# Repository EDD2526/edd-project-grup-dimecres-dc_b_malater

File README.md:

View this project on [CADLAB.io](https://cadlab.io/project/30194). 

# Projecte Maleter 

>**Autors: Alba Martin i Mireia Campanera
<<<<<<< HEAD
>**Versió: 
=======
>**Versió: 1
>>>>>>> 689ee14ca79a34b128441d443d3a97a18ecf9688

----------

## Objectiu

>PCB per 
 - Obrir i tancar el maleter amb un motor
 - Detectar el peu sota el cotxe per obrir-lo
 - Activar el calefactor del vidre del maleter
 - Detectar objectes per evitar atrapaments

## Diagrama de blocs
<<<<<<< HEAD

=======

>>>>>>> 689ee14ca79a34b128441d443d3a97a18ecf9688
### Descripció/funcionalitat de cada bloc

  * El motor pot funcionar amb 12V de la bateria, però el microcontrolador en necessita 3.3V, per tant hem de posar reguladors de tensió que la redueixin.[Baixem de 12 a 5V (LM2596)] [Baixem de 5 a 3.3V (LM1117)]
  * Motor DC: un motor DC té dos cables, quan connectem una bateria, connectem un a 12V i l’altre a GND, i el motor comença a girar en un sentit. Què passa si canviem els cables? si invertim la polaritat, el motor gira cap a l’altre costat. Això ho necessitem perquè el maleter necessita dues accions: obrir i tancar. Per tant el motor ha de poder girar: sentit 1 —> obrir,, sentit 2—> tancar.
  * DRIVER DE MOTOR (H-Bridge):
El driver és un circuit que ens permet:
controlar el motor
canviar el sentit de gir*
controlar la velocitat (PWM)
En el nostre cas utilitzarem el DRV8871
  * SENSOR D’OBERTURA AMB EL PEU:
El cotxe detecta el peu sota el para-xocs, això ho fa amb un sensor de distància. Nosaltres hem triat el ToF VL53L0X  (Time of Flight). Mesura la distància amb llum infraroja. Aquesta informació la envia al micro amb un sistema de comunicació anomenat I2C, aquest, permet que dos circuits parlin entre ells. Només necessita dos cables: SDA(Serial Data), cable per on passen les dades i SCL(Serial Clock), cable que marca el ritme de comunicació.
  * SENSOR DE FINAL DE CARRERA:
Detecta si el maleter està totalment obert. És simplement un interruptor mecànic, quan el maleter està tancat l’interruptor està en OFF, quan està obert està en ON. 
  * SENSOR ANTI-ATRAPAMENT:
Evita que t’atrapis la mà amb el maleter.
Això ho evitarem detectant quan el motor està bloquejat (per una mà atrapada). Quan el motor es bloqueja la corrent del motor augmenta molt, detectant aquest augment de corrent és com evitarem l’atrapament. Això ho farem amb un circuit de tres parts:
Resistència molt petita (0.05Ω) entre el motor i el GND
quan passa corrent per una resistència tan petita la tensió serà proporcional al corrent que circuli per aquesta. Per tant, si circula un corrent normal (petit) obtindrem tensió petita.
Amplificador INA180
aquest tensió és massa petita per al micro, per això necessitem un amplificador de corrent. Així el micro ho podrà mesurar.
Microcontrolador
el micro rep aquesta tensió al seu ADC. L’ ADC és un pin que pot mesurar voltatge.
  * CALEFACTOR DEL VIDRE:
El vidre del maleter té una resistència calefactora que funciona amb 12V i 3A - 5A, per tant el microcontrolador no pot alimentar-lo directament, hem de fer servir un MOSFET. Aquest funciona com un interruptor electrònic, quan el micro activa el MOSFET el calefactor s’encén.

-----------

## Requisits / Especificacions

<<<<<<< HEAD
  * Alimentació; 12V, regulada 5V (LM2596), regulada 3.3V (LM1117)
  * Microcontrolador PIC24HJ128GP502
  * Driver Motor DRV8871
  * Sensor d'obertura amb el peu ToF VL53L0X  
  * Sensor final de carrera microswitch kw11
  * Sensor anti-atrapament (amplificador INA180)
  * Calefactor (mosfet)
  * Comunicació Can MCP2551
=======
  * Alimentació; 12V, regulada 5V
  * Microcontrolador PIC24HJ128GP502
  * ...
>>>>>>> 689ee14ca79a34b128441d443d3a97a18ecf9688

-----------

## Components (Veure datasheets en la carpeta datasheet)

| Descripci&#243; | Ref | Package |Datasheet | Prove&#239;dor | Preu | Unitats |
| --- | --- | --- | --- | ---| --- | --- |
| Microcontrolador | PIC18F26Q83-I/SS | SOIC-28 |[Datasheet](https://www.mouser.es/datasheet/2/268/PIC18F27_47_57Q83_Preliminary_Data_Sheet_40002265B-2887591.pdf) | [Mouser](https://www.mouser.es/c/?q=PIC18F27Q83-I%2FSO)| 2,17&euro;| 1x |
| XTAL-Ressonador | CSTCR7M99G53-R0 | SMD |[Datasheet](https://www.mouser.es/datasheet/2/281/p16e-522700.pdf) | [Mouser](https://www.mouser.es/ProductDetail/Murata-Electronics/CSTCR7M99G53-R0?qs=Zd9RUO93%2Fo7cnwzsujIkpA%3D%3D)  | 0,27&euro; | 1x |

-----------

## Software

### Eines:

  * KiCad 9.0 o superior
  * 

### Configuraci&#243; :

  * 

### Funcionalitats:

  * 

-----------

## Historial de canvis

| Data | Autor     | Branch | Versi&#243; | Descripci&#243; |
| --- | --- | --- | --- | --- |
|  28/03/2023 | mlopez | Master | initial commit | Primera versi&#243; d'esquem&#224;tic i selecci&#243; de components |

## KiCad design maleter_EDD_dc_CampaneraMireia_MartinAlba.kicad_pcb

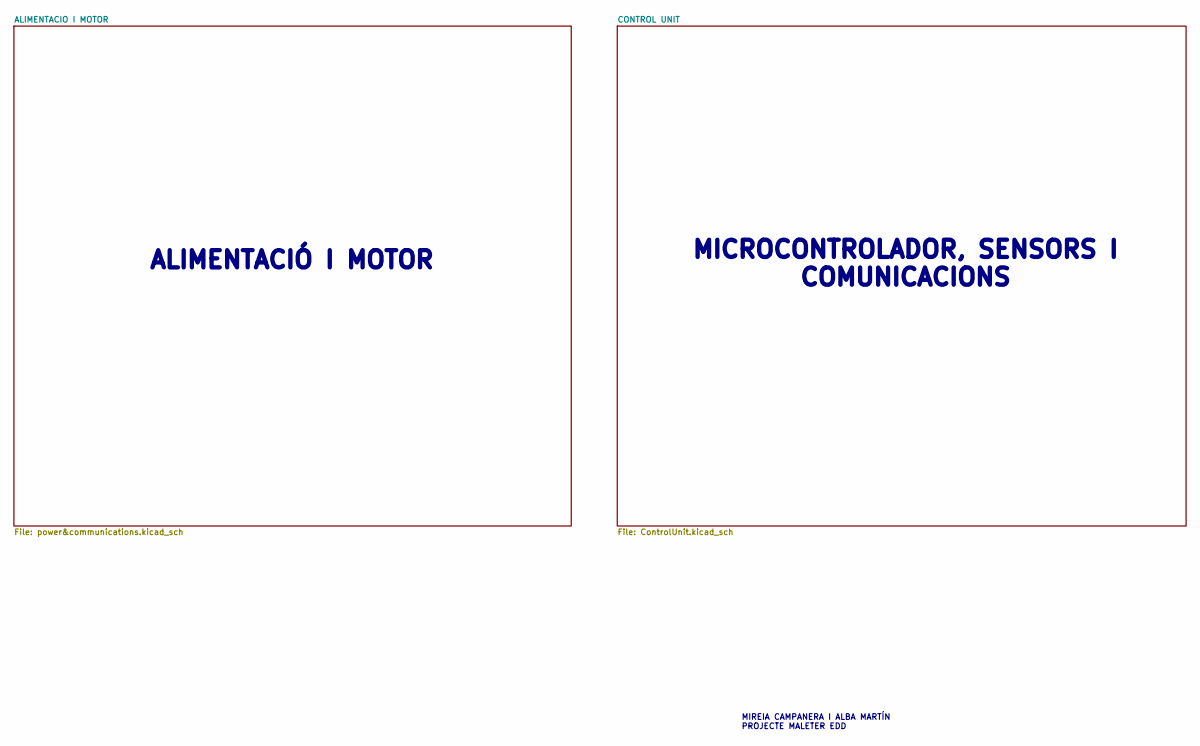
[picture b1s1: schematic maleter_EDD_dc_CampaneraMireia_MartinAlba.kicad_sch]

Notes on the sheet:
MIREIA CAMPANERA I ALBA MARTÍN PROJECTE MALETER EDD
ALIMENTACIÓ I MOTOR
MICROCONTROLADOR, SENSORS I COMUNICACIONS

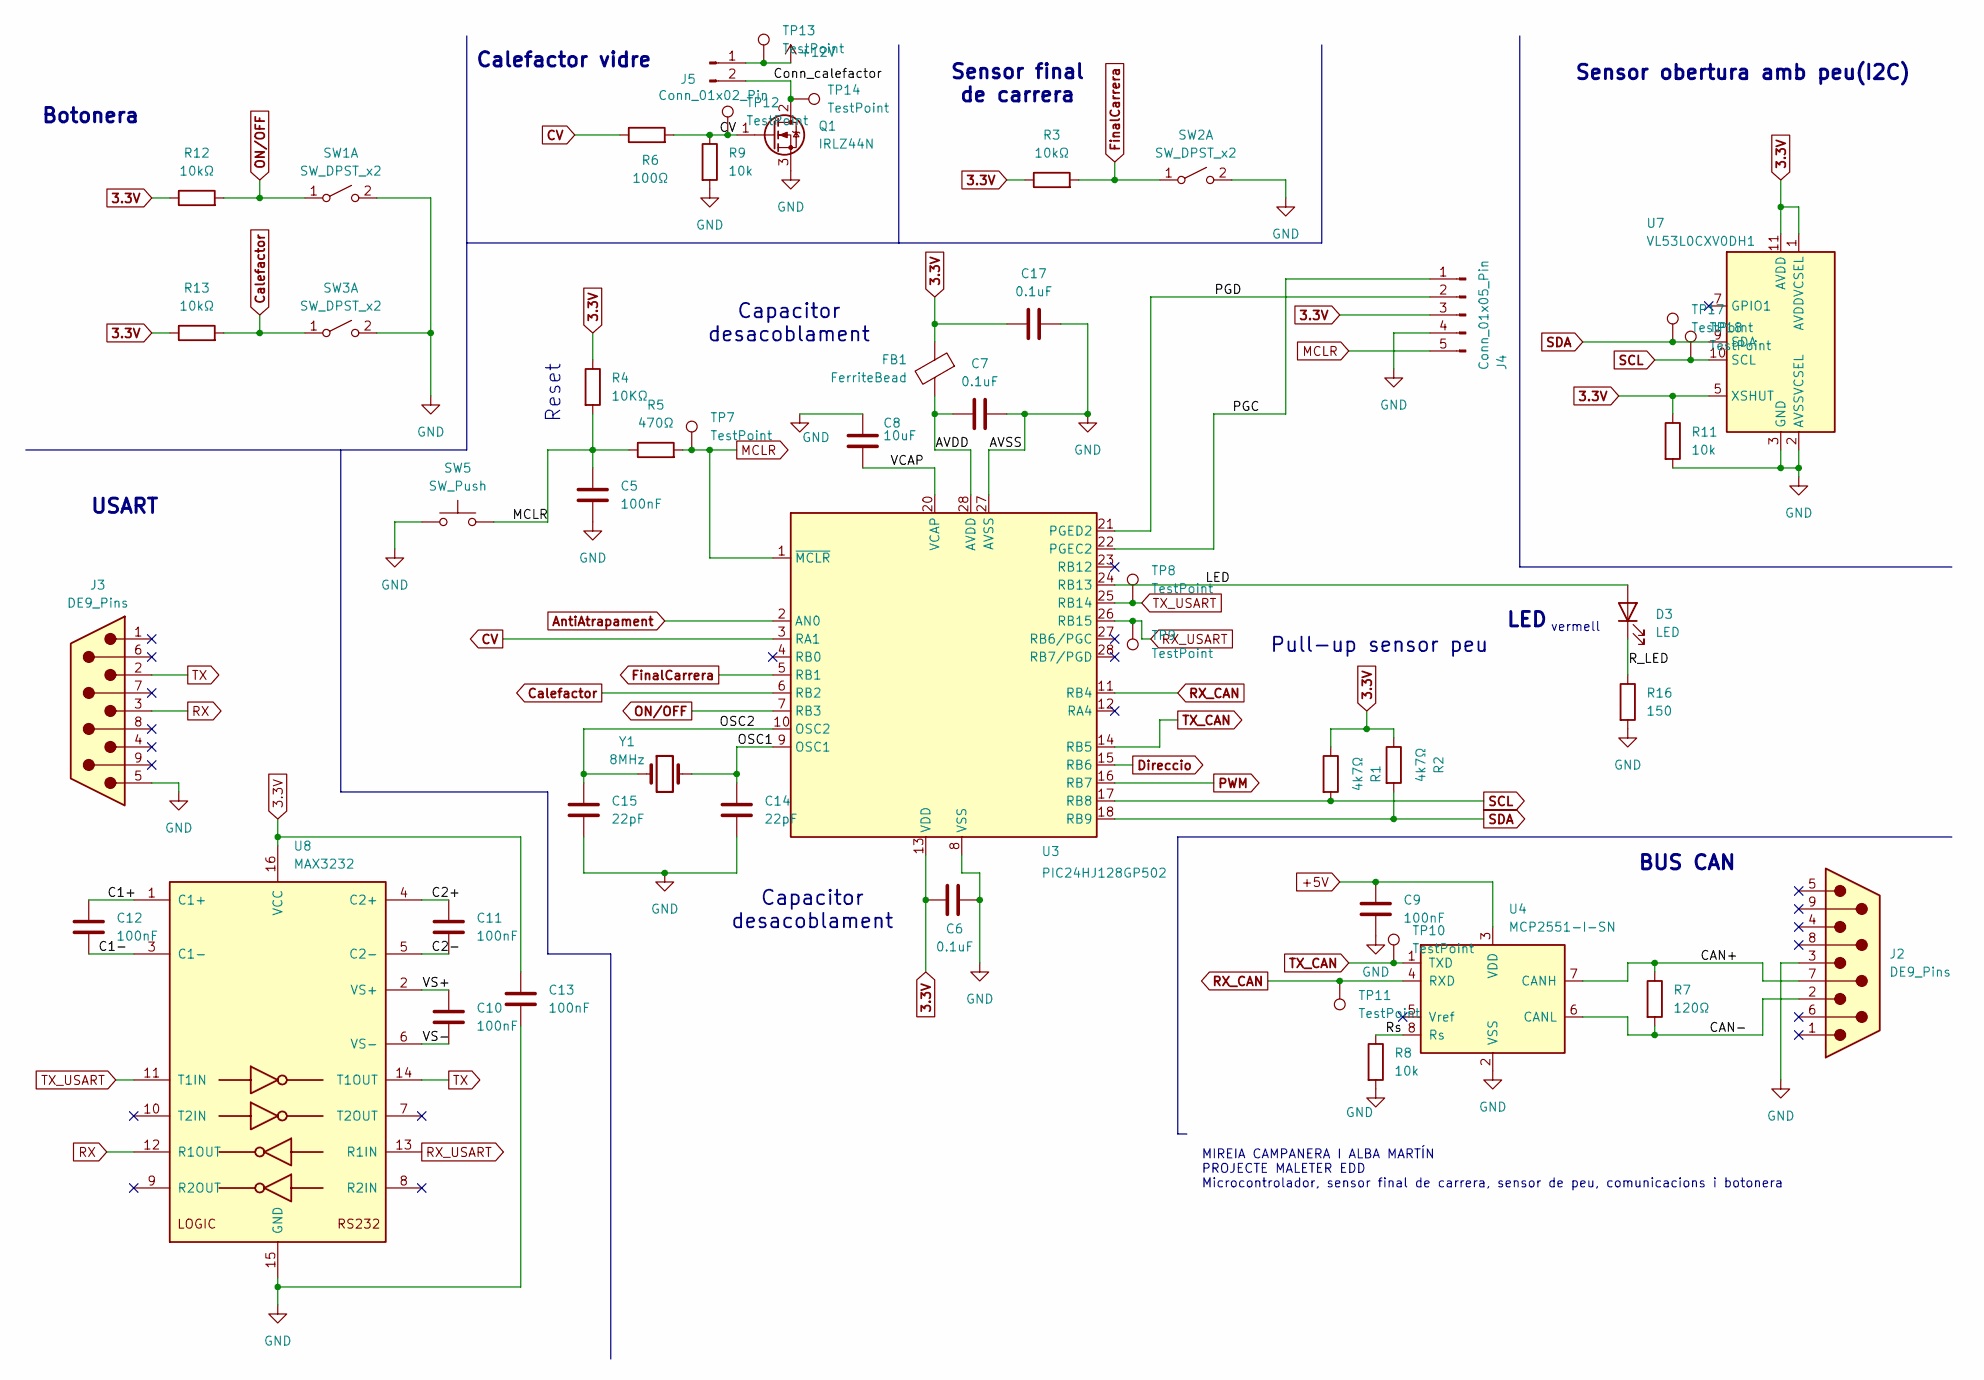
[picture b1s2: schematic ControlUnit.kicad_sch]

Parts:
C5, C9, C10, C11, C12, C13: 100nF; C_0201_0603Metric
C6, C7, C17: 0.1uF; C_0201_0603Metric
C8: 10uF; C_0201_0603Metric
C14, C15: 22pF; C_0201_0603Metric
D3: LED; LED_0201_0603Metric
FB1: FerriteBead; L_0201_0603Metric
J2, J3: DE9_Pins; DSUB-9_Pins_Horizontal_P2.77x2.84mm_EdgePinOffset9.40mm
J4: Conn_01x05_Pin; PinSocket_1x05_P1.27mm_Vertical
J5: Conn_01x02_Pin; PinSocket_1x02_P1.27mm_Vertical
Q1: IRLZ44N; TO-220-3_Vertical
R1, R2: 4k7Ω; R_0201_0603Metric
R3, R12, R13: 10kΩ; R_0201_0603Metric
R4: 10KΩ; R_0201_0603Metric
R5: 470Ω; R_0201_0603Metric
R6: 100Ω; R_0201_0603Metric
R7: 120Ω; R_0201_0603Metric
R8, R9, R11: 10k; R_0201_0603Metric
R16: 150; R_0201_0603Metric
SW1, SW2, SW3: SW_DPST_x2; SW_DIP_SPSTx02_Slide_6.7x6.64mm_W6.73mm_P2.54mm_LowProfile_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
SW5: SW_Push; SW_PUSH_6mm
TP7, TP8, TP9, TP10, TP11, TP12, TP13, TP14, TP17, TP18: TestPoint; TestPoint_Pad_D1.0mm
U3: PIC24HJ128GP502; SSOP-28_5.3x10.2mm_P0.65mm
U4: MCP2551-I-SN; SOIC-8_3.9x4.9mm_P1.27mm
U7: VL53L0CXV0DH1; ST_VL53L1x
U8: MAX3232; SOIC-16W_5.3x10.2mm_P1.27mm
Y1: 8MHz; Crystal_HC49-4H_Vertical

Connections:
3.3V: C6.1, C13.1, C17.1, FB1.1, J4.3, R1.1, R2.1, R3.1, R4.1, R11.1, R12.1, R13.1, U3.13 (VDD), U7.1 (AVDDVCSEL), U7.5 (XSHUT), U7.11 (AVDD), U8.16 (VCC); also elsewhere on the board
+5V: C9.1, U4.3 (VDD); also elsewhere on the board
+12V: J5.1, TP13.1; also elsewhere on the board
/CONTROL UNIT/AVDD: C7.1, FB1.2, U3.28 (AVDD)
/CONTROL UNIT/C1+: C12.1, U8.1 (C1+)
/CONTROL UNIT/C1-: C12.2, U8.3 (C1-)
/CONTROL UNIT/C2+: C11.1, U8.4 (C2+)
/CONTROL UNIT/C2-: C11.2, U8.5 (C2-)
/CONTROL UNIT/CAN+: J2.7, R7.1, U4.7 (CANH)
/CONTROL UNIT/CAN-: J2.2, R7.2, U4.6 (CANL)
/CONTROL UNIT/Conn_calefactor: J5.2, Q1.2 (D), TP14.1
/CONTROL UNIT/LED: D3.2 (A), U3.24 (RB13)
/CONTROL UNIT/OSC1: C14.1, U3.9 (OSC1), Y1.2
/CONTROL UNIT/OSC2: C15.1, U3.10 (OSC2), Y1.1
/CONTROL UNIT/PGC: J4.1, U3.22 (PGEC2)
/CONTROL UNIT/PGD: J4.2, U3.21 (PGED2)
/CONTROL UNIT/R_LED: D3.1 (K), R16.1
/CONTROL UNIT/Rs: R8.1, U4.8 (Rs)
/CONTROL UNIT/VCAP: C8.2, U3.20 (VCAP)
/CONTROL UNIT/VS+: C10.1, U8.2 (VS+)
/CONTROL UNIT/VS-: C10.2, U8.6 (VS-)
AntiAtrapament: U3.2 (AN0); also elsewhere on the board
CV: Q1.1 (G), R6.1, R6.2, R9.1, TP12.1, U3.3 (RA1)
Calefactor: R13.2, SW3.1 (A), U3.6 (RB2)
Direccio: U3.15 (RB6); also elsewhere on the board
FinalCarrera: R3.2, SW2.1 (A), U3.5 (RB1)
GND: C5.2, C6.2, C7.2, C8.1, C9.2, C13.2, C14.2, C15.2, C17.2, J2.3, J3.5, J4.4, Q1.3 (S), R8.2, R9.2, R11.2, R16.2, SW1.2 (B), SW2.2 (B), SW3.2 (B), SW5.1, U3.8 (VSS), U3.27 (AVSS), U4.2 (VSS), U7.2 (AVSSVCSEL), U7.3 (GND), U7.4 (GND), U7.6 (GND), U7.12 (GND), U8.15 (GND); also elsewhere on the board
MCLR: C5.1, J4.5, R4.2, R5.1, R5.2, SW5.2, TP7.1, U3.1 (~MCLR)
ON/OFF: R12.2, SW1.1 (A), U3.7 (RB3)
PWM: U3.16 (RB7); also elsewhere on the board
RX: J3.3, U8.12 (R1OUT)
RX_CAN: TP11.1, U3.11 (RB4), U4.4 (RXD)
RX_USART: TP9.1, U3.26 (RB15), U8.13 (R1IN)
SCL: R1.2, TP18.1, U3.17 (RB8), U7.10 (SCL)
SDA: R2.2, TP17.1, U3.18 (RB9), U7.9 (SDA)
TX: J3.2, U8.14 (T1OUT)
TX_CAN: TP10.1, U3.14 (RB5), U4.1 (TXD)
TX_USART: TP8.1, U3.25 (RB14), U8.11 (T1IN)

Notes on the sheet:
Capacitor desacoblament
Sensor final de carrera
Calefactor vidre
Sensor obertura amb peu(I2C)
Pull-up sensor peu
LED
USART
MIREIA CAMPANERA I ALBA MARTÍN PROJECTE MALETER EDD Microcontrolador, sensor final de carrera, sensor de peu, comunicacions i botonera
Botonera
BUS CAN
vermell
Reset

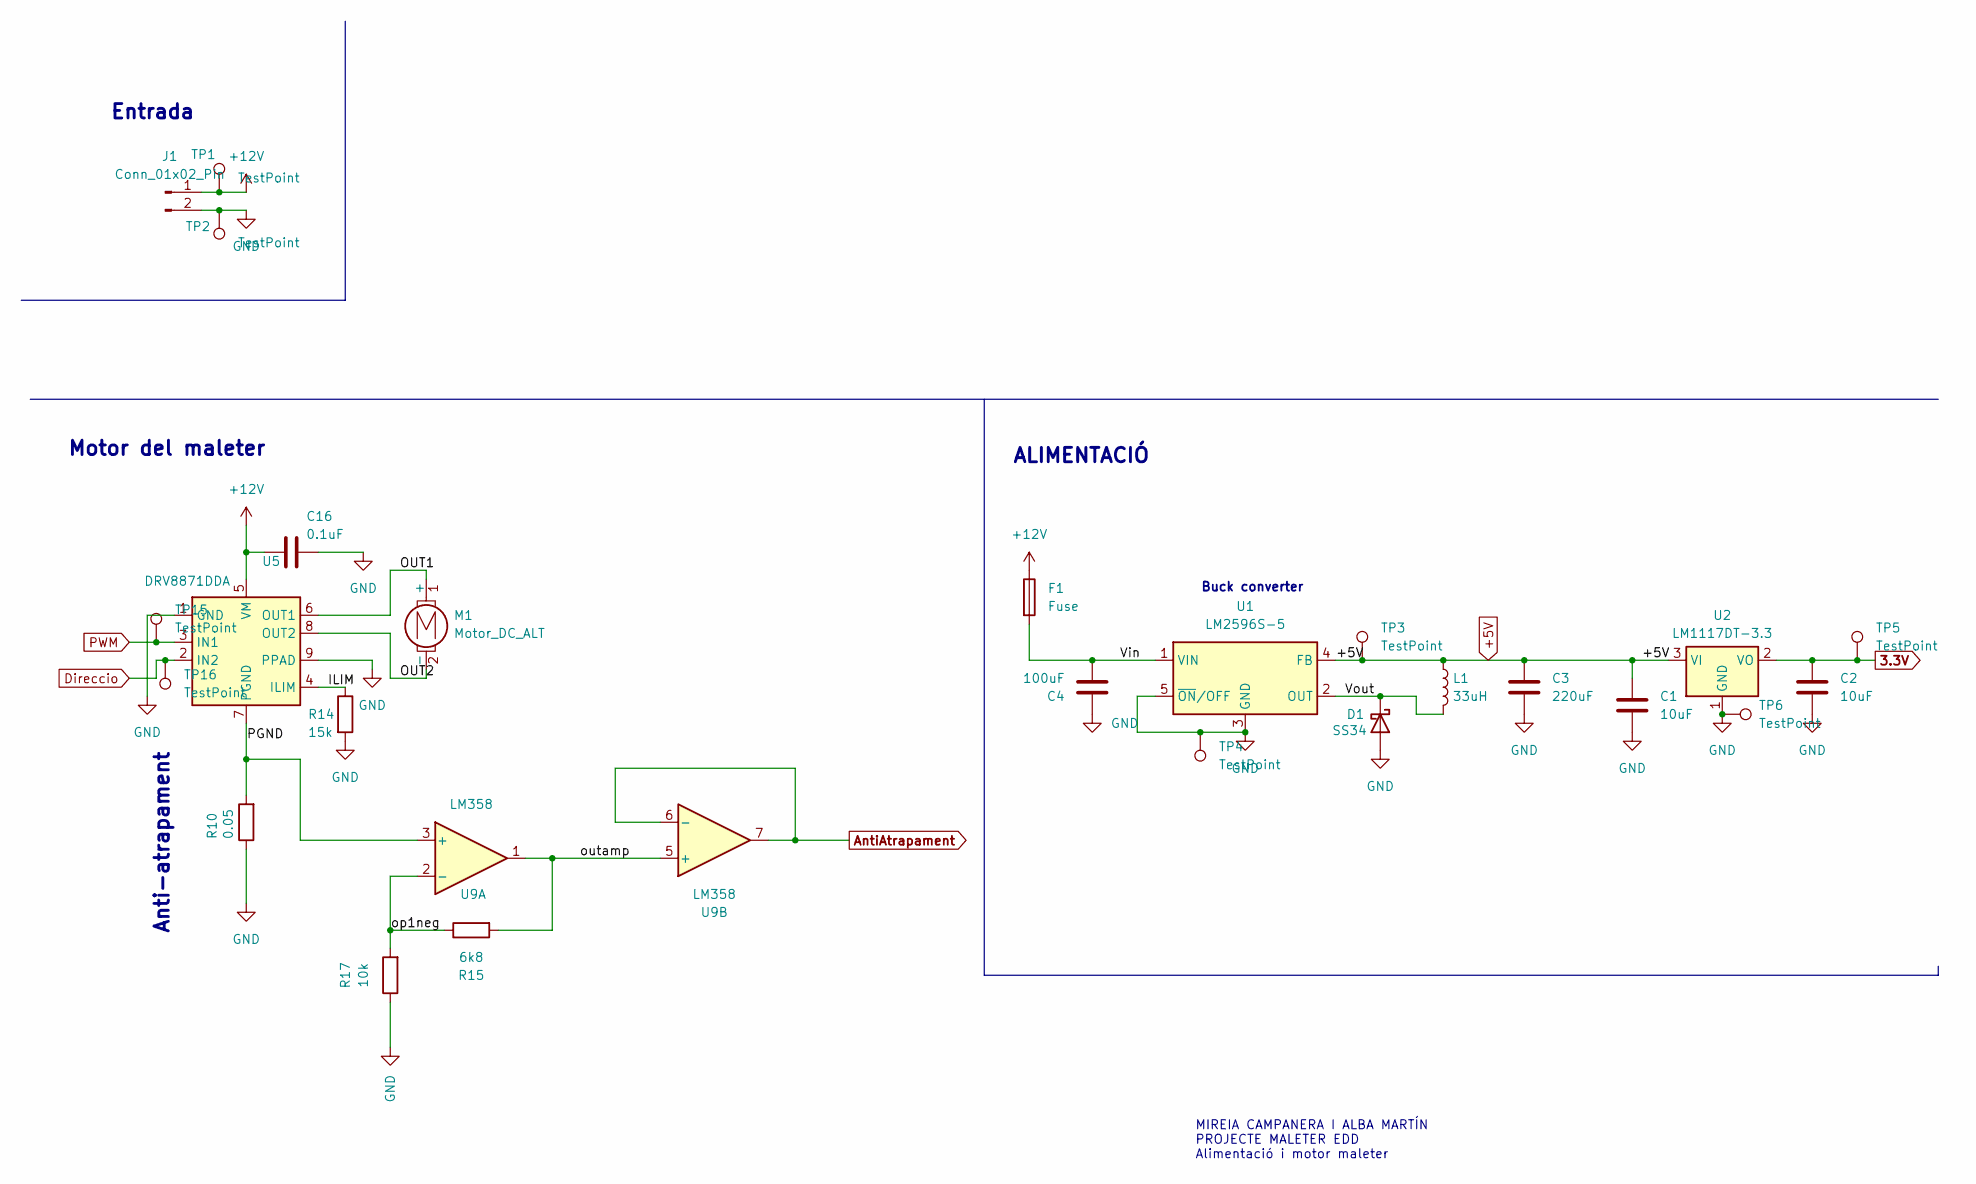
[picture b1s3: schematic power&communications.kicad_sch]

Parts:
C1, C2: 10uF; C_0201_0603Metric
C3: 220uF; C_0201_0603Metric
C4: 100uF; C_0201_0603Metric
C16: 0.1uF; C_0201_0603Metric
D1: SS34; D_SMA
F1: Fuse; Fuse_0402_1005Metric
J1: Conn_01x02_Pin; PinSocket_1x02_P1.27mm_Vertical
L1: 33uH; L_6.3x6.3_H3
M1: Motor_DC_ALT; TerminalBlock_CUI_TB007-508-02_1x02_P5.08mm_Horizontal
R10: 0.05; R_0201_0603Metric
R14: 15k; R_0201_0603Metric
R15: 6k8; R_1206_3216Metric
R17: 10k; R_1206_3216Metric
TP1, TP2, TP3, TP4, TP5, TP6, TP15, TP16: TestPoint; TestPoint_Pad_D1.0mm
U1: LM2596S-5; TO-263-5_TabPin3
U2: LM1117DT-3.3; TO-252-3_TabPin2
U5: DRV8871DDA; Texas_HTSOP-8-1EP_3.9x4.9mm_P1.27mm_EP2.95x4.9mm_Mask2.4x3.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
U9: LM358; SOIC-8_5.3x6.2mm_P1.27mm

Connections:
3.3V: C2.1, TP5.1, U2.2 (VO); also elsewhere on the board
+5V: C1.1, C3.1, L1.1, TP3.1, U1.4 (FB), U2.3 (VI); also elsewhere on the board
+12V: C16.2, F1.1, J1.1, TP1.1, U5.5 (VM); also elsewhere on the board
/ALIMENTACIO I MOTOR/ILIM: R14.1, U5.4 (ILIM)
/ALIMENTACIO I MOTOR/OUT1: M1.1 (+), U5.6 (OUT1)
/ALIMENTACIO I MOTOR/OUT2: M1.2 (-), U5.8 (OUT2)
/ALIMENTACIO I MOTOR/PGND: R10.2, U5.7 (PGND), U9.3 (+)
/ALIMENTACIO I MOTOR/Vin: C4.2, F1.2, U1.1 (VIN)
/ALIMENTACIO I MOTOR/Vout: D1.1 (K), L1.2, U1.2 (OUT)
/ALIMENTACIO I MOTOR/op1neg: R15.1, R17.2, U9.2 (-)
/ALIMENTACIO I MOTOR/outamp: R15.2, U9.1, U9.5 (+)
AntiAtrapament: U9.6 (-), U9.7; also elsewhere on the board
Direccio: TP16.1, U5.2 (IN2); also elsewhere on the board
GND: C1.2, C2.2, C3.2, C4.1, C16.1, D1.2 (A), J1.2, R10.1, R14.2, R17.1, TP2.1, TP4.1, TP6.1, U1.3 (GND), U1.5 (~ON/OFF), U2.1 (GND), U5.1 (GND), U5.9 (PPAD); also elsewhere on the board
PWM: TP15.1, U5.3 (IN1); also elsewhere on the board

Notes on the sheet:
Buck converter
Anti-atrapament
Motor del maleter
ALIMENTACIÓ
MIREIA CAMPANERA I ALBA MARTÍN PROJECTE MALETER EDD Alimentació i motor maleter
Entrada

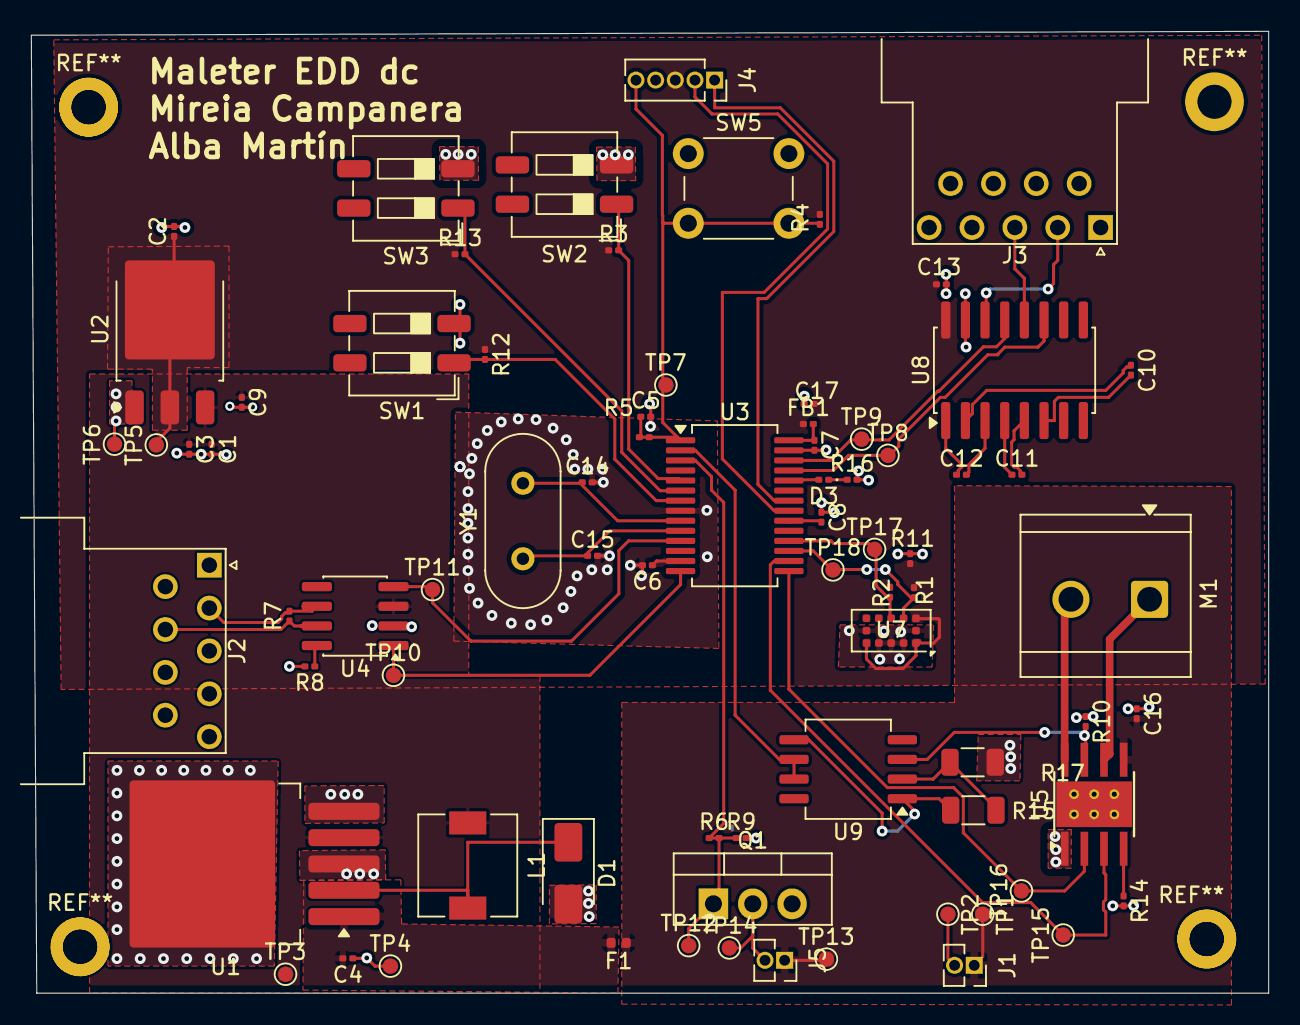
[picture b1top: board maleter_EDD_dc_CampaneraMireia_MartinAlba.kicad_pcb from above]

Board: 2 copper layers, 80.0 x 62.2 mm, 77 parts (0 on the bottom side), 46 nets.

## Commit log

2026-03-11 Readme prova
2026-03-11 Backlink to CADLAB.io has been added.
2026-03-17 Afegit els datasheets
2026-03-17 esquemàtic complet maleter
2026-03-23 Actualització projecte KiCad
2026-03-23 Neteja carpeta
2026-03-23 Definició parcial huellas
2026-03-23 cristall
2026-03-23 Botonera
2026-03-23 cristall, switch i huellas
2026-03-23 coses que falten
2026-03-23 readme
2026-03-24 readmev.2
2026-03-24 Correccions professor
2026-03-24 Captura diagrama de blocs a readme
2026-04-07 Ultima versio projecte
2026-04-07 layout v1
2026-04-07 layout v2
2026-04-07 lay out
2026-04-07 emplenar plans de massa
2026-04-08 Actualització projecte a classe
2026-04-09 hola
2026-04-14 Millores profe pcb
2026-04-14 mes canvis
2026-04-15 Canvis pcb classe
2026-04-21 actualizacio placa drl
2026-04-24 casi esquematic acabat
2026-04-27 versio final
2026-04-28 pressupost
